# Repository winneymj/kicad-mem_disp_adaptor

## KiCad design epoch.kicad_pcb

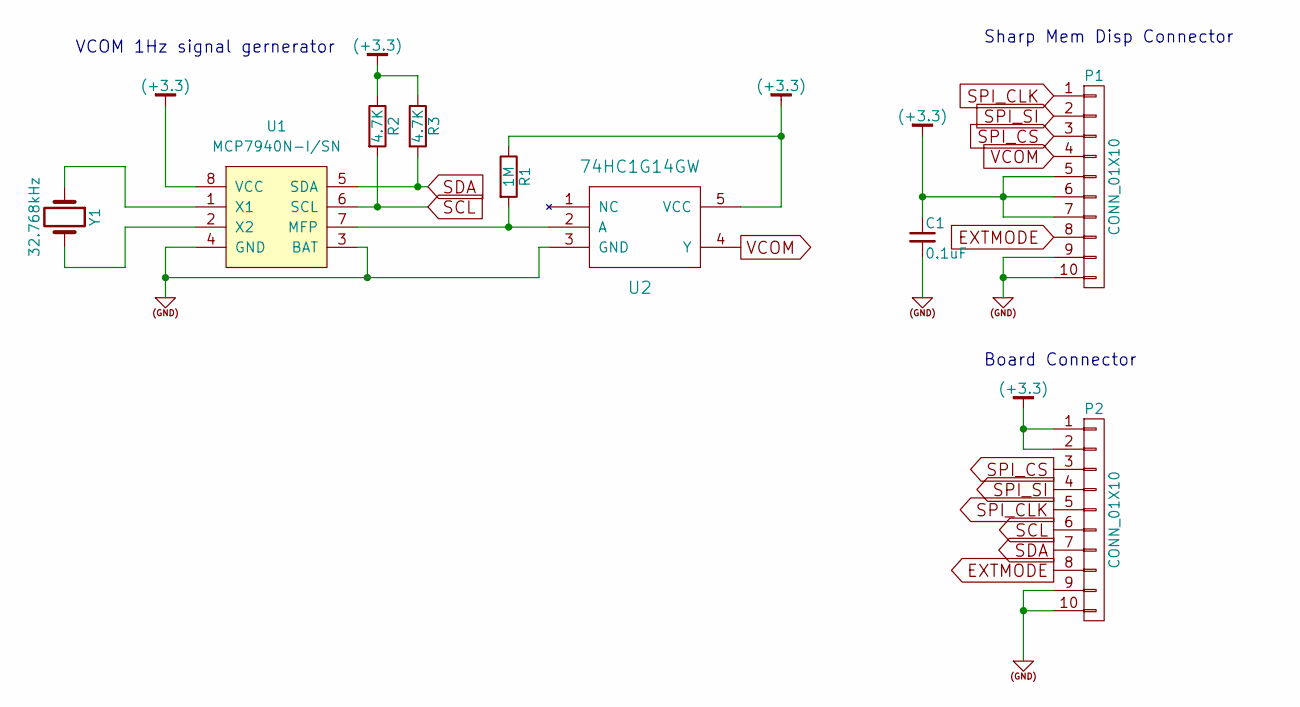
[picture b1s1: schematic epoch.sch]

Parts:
C1: 0.1uF; C_0805_HandSoldering
P1: CONN_01X10; MOLEX_0.5MM_505278
P2: CONN_01X10; Pin_Header_Straight_1x10_Pitch2.54mm
R1: 1M; R_0805_HandSoldering
R2, R3: 4.7K; R_0805_HandSoldering
U1: MCP7940N-I/SN; SOIC-8_3.9x4.9mm_Pitch1.27mm; MPN MCP7940N-I/SN
U2: 74HC1G14GW; SOT-353_SC-70-5_Handsoldering
Y1: 32.768kHz; Crystal_SMD_Citizen_CM200C_7.9_x_3.7

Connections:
(+3.3): C1.1, P1.5, P1.6, P1.7, P2.1, P2.2, R1.1, R2.1, R3.1, U1.8 (VCC), U2.5 (VCC)
(GND): C1.2, P1.9, P1.10, P2.9, P2.10, U1.3 (BAT), U1.4 (GND), U2.3 (GND)
EXTMODE: P1.8, P2.8
unnamed: R1.2, U1.7 (MFP), U2.2 (A)
unnamed: U1.1 (X1), Y1.1
unnamed: U1.2 (X2), Y1.2
SCL: P2.6, R2.2, U1.6 (SCL)
SDA: P2.7, R3.2, U1.5 (SDA)
SPI_CLK: P1.1, P2.5
SPI_CS: P1.3, P2.3
SPI_SI: P1.2, P2.4
VCOM: P1.4, U2.4 (Y)

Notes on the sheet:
Sharp Mem Disp Connector
VCOM 1Hz signal gernerator
Board Connector

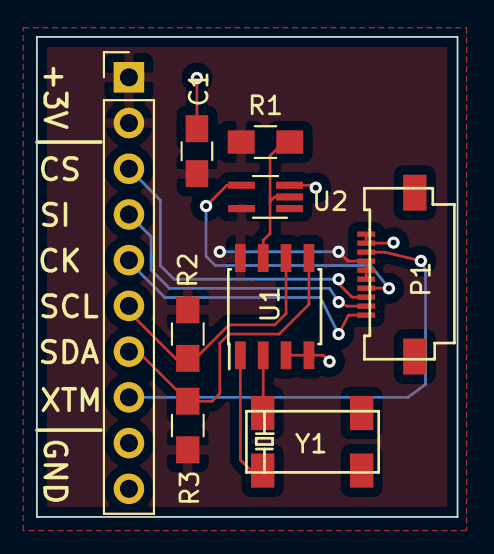
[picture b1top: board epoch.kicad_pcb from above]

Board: 2 copper layers, 23.4 x 26.7 mm, 9 parts (0 on the bottom side), 12 nets.

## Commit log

2017-03-14 Save gerbers
